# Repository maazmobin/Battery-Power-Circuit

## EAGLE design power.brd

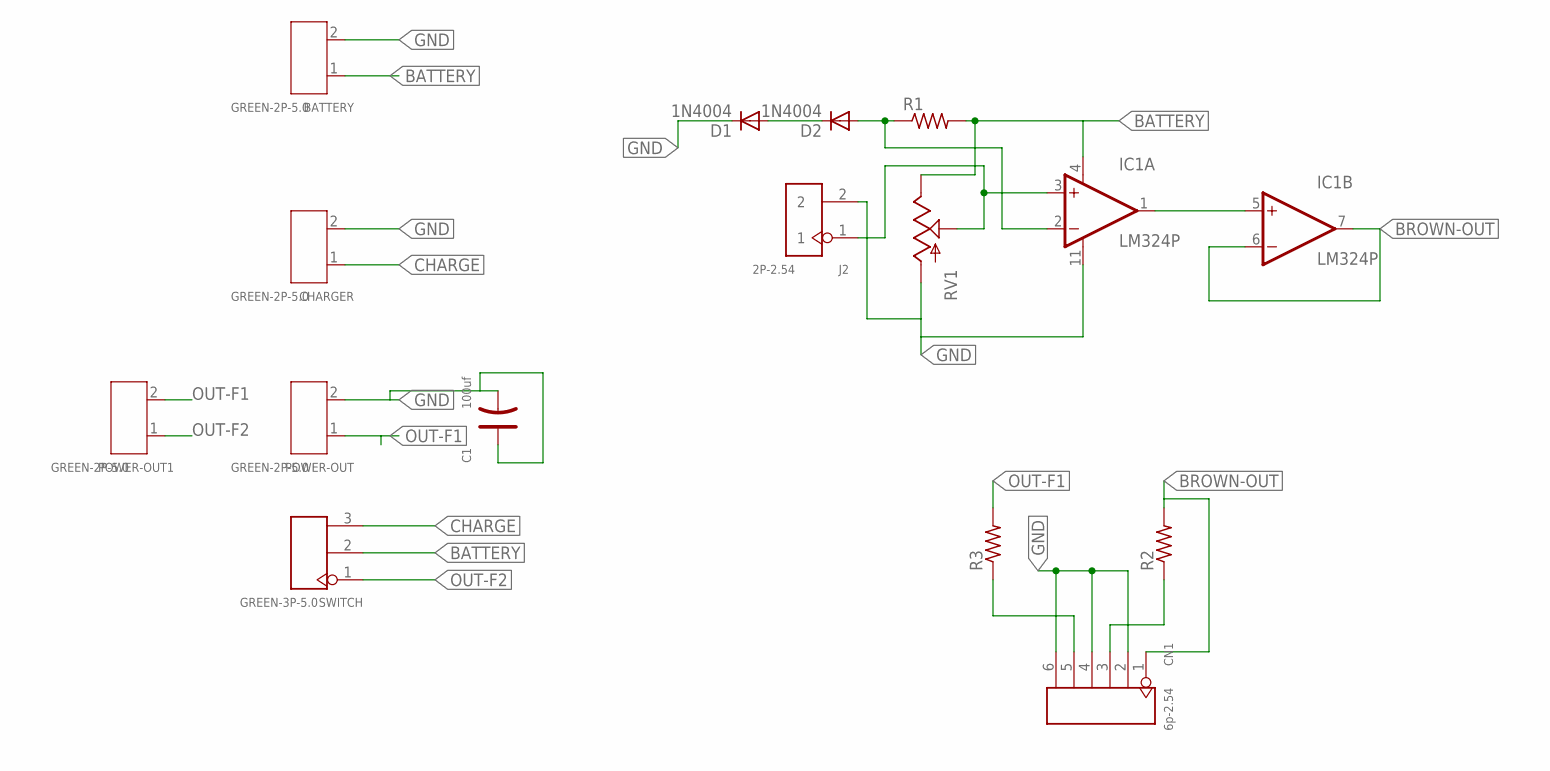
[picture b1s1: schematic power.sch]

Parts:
BATTERY: GREEN-2P-5.0; H2-5.0-10.5X8.0MM
C1: 100uf; PC-D5.3MM
CHARGER: GREEN-2P-5.0; H2-5.0-10.5X8.0MM
CN1: 6p-2.54; H6-2.54
D1, D2: 1N4004; DO41-10
IC1: LM324P; DIL14
J2: 2P-2.54; H2-2.54
POWER-OUT, POWER-OUT1: GREEN-2P-5.0; H2-5.0-10.5X8.0MM
R1, R2, R3: R-US_0207/10; 0207/10
RV1: POTTRIM; TRIM_POT
SWITCH: GREEN-3P-5.0; H3-5.0-15.5X8.0MM

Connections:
BATTERY: BATTERY.1, IC1.4 (V+), R1.2, RV1.2 (E), SWITCH.2
BROWN-OUT: CN1.1, IC1.6 (-IN), IC1.7 (OUT), R2.2
CHARGE: CHARGER.1, SWITCH.3
GND: BATTERY.2, C1.+, C1.-, CHARGER.2, CN1.2, CN1.4, CN1.6, D1.C, IC1.11 (V-), J2.2, POWER-OUT.2, RV1.3 (A)
unnamed: CN1.5, R3.1
unnamed: D1.A, D2.C
unnamed: D2.A, IC1.2 (-IN), R1.1
unnamed: IC1.3 (+IN), J2.1, RV1.1 (S)
unnamed: IC1.1 (OUT), IC1.5 (+IN)
unnamed: CN1.3, R2.1
OUT-F1: POWER-OUT.1, POWER-OUT1.2, R3.2
OUT-F2: POWER-OUT1.1, SWITCH.1

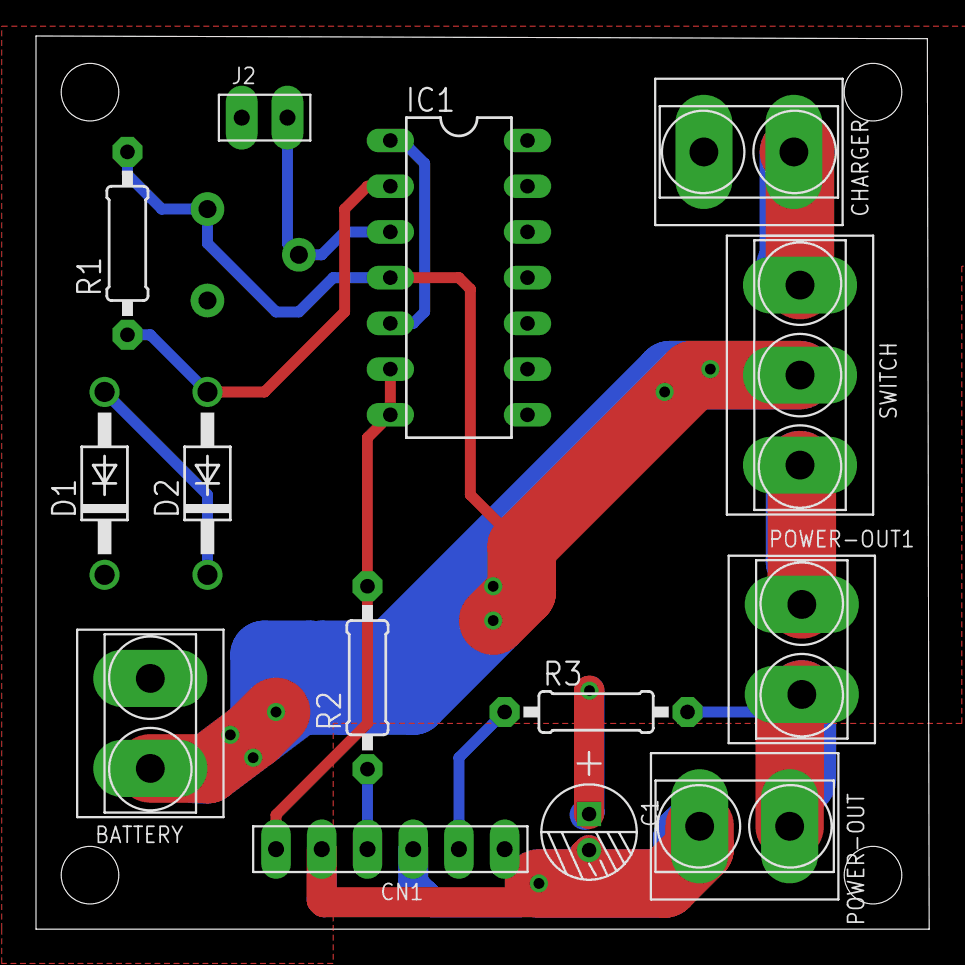
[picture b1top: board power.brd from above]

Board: 2 copper layers, 49.6 x 49.6 mm, 15 parts (0 on the bottom side), 12 nets.

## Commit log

2017-03-13 :circus_tent: Added .gitattributes & .gitignore files
2017-03-13 Done board
    DONE
    5x5cm
    Signal width: 0.024
    Required:
    Double check schematic

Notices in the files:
parts and their libraries:
SparkFun-Electromechanical: Licensing: Creative Commons ShareAlike 4.0 International - https://creativecommons.org/licenses/by-sa/4.0
